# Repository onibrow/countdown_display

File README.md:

# Countdown Display

A low power countdown display

## Manual

### On / Off

The slide switch in the right position (closer to the edge of the device) is the "Discharge" or ON mode. The slide switch in the left position (closer to the middle of the device) is the "Charge / OFF" mode.

### Charging

To charge the battery, put the slide switch into the "Charge / OFF" mode - this will disconnect the battery from the rest of the device and enable it to be charged. At this state, the display will no longer turn on. Plug in a microUSB cable to the port and watch the indicator LED turn on. If RED, the battery is charging - if GREEN, the charge is complete. From fully discharged to fully charged, it will take about 2.5 hours.

### Safety

As this device has all of its electrical components exposed, do not touch this with wet hands or poke it with metal / conductive objects. There are safety electronics in play to prevent the battery from over-currenting and frying itself, it is generally not a great idea to mess around with LiPo batteries. 

## Features

### 128x32 OLED Display

[SSD1306](https://smile.amazon.com/gp/product/B07X35H728/ref=ppx_yo_dt_b_asin_title_o06_s00?ie=UTF8&psc=1) 128x32 OLED display compatible with Adafruit's [OLED library](https://github.com/adafruit/Adafruit_SSD1306), featuring a shut down mode for low power consumption, capable of running off 3.6V to 5V.

### Low Power

ATMega328P was chosen for the microcontroller of choice, for its low power sleep feature and small footprint. Running off of a LiPo battery, it can enter a deep sleep that consumes less that 10uA of current utilizing the external interrupt (generated using a push button) based indefinite sleep, from the [Arduino LowPower library](https://www.arduino.cc/en/Reference/ArduinoLowPower). The fuses are burned to use an 8MHz external clock and to brown out at 3V.

### RTC

A real time clock was used to keep track of the current date and time, running off of an ultra low power DS3231 and a back up coin cell. With the coin cell, the time keeping feature can run for 5 years, while the ultra low power could be directly sourced from one of the digital output pins on the ATMega to make power on and off of the RTC much easier. The Adafrtui [RTClib](https://github.com/adafruit/RTClib) was used for this chip.

### LiPo

A 40mAh LiPo battery was chosen as the main power supply for this device. Considering an ON current of about 12mA and a deep sleep current of 10uA, a quick calculation assuming that the device will be powered on for 2 minutes in any given day leaves the device an astounding 2 month life on a single charge. It is also equiped with an [MCP73831](https://www.microchip.com/wwwproducts/en/en024903) single cell, LiPo charge management controller to recharge the battery safely over a microUSB connection.

## Gallery

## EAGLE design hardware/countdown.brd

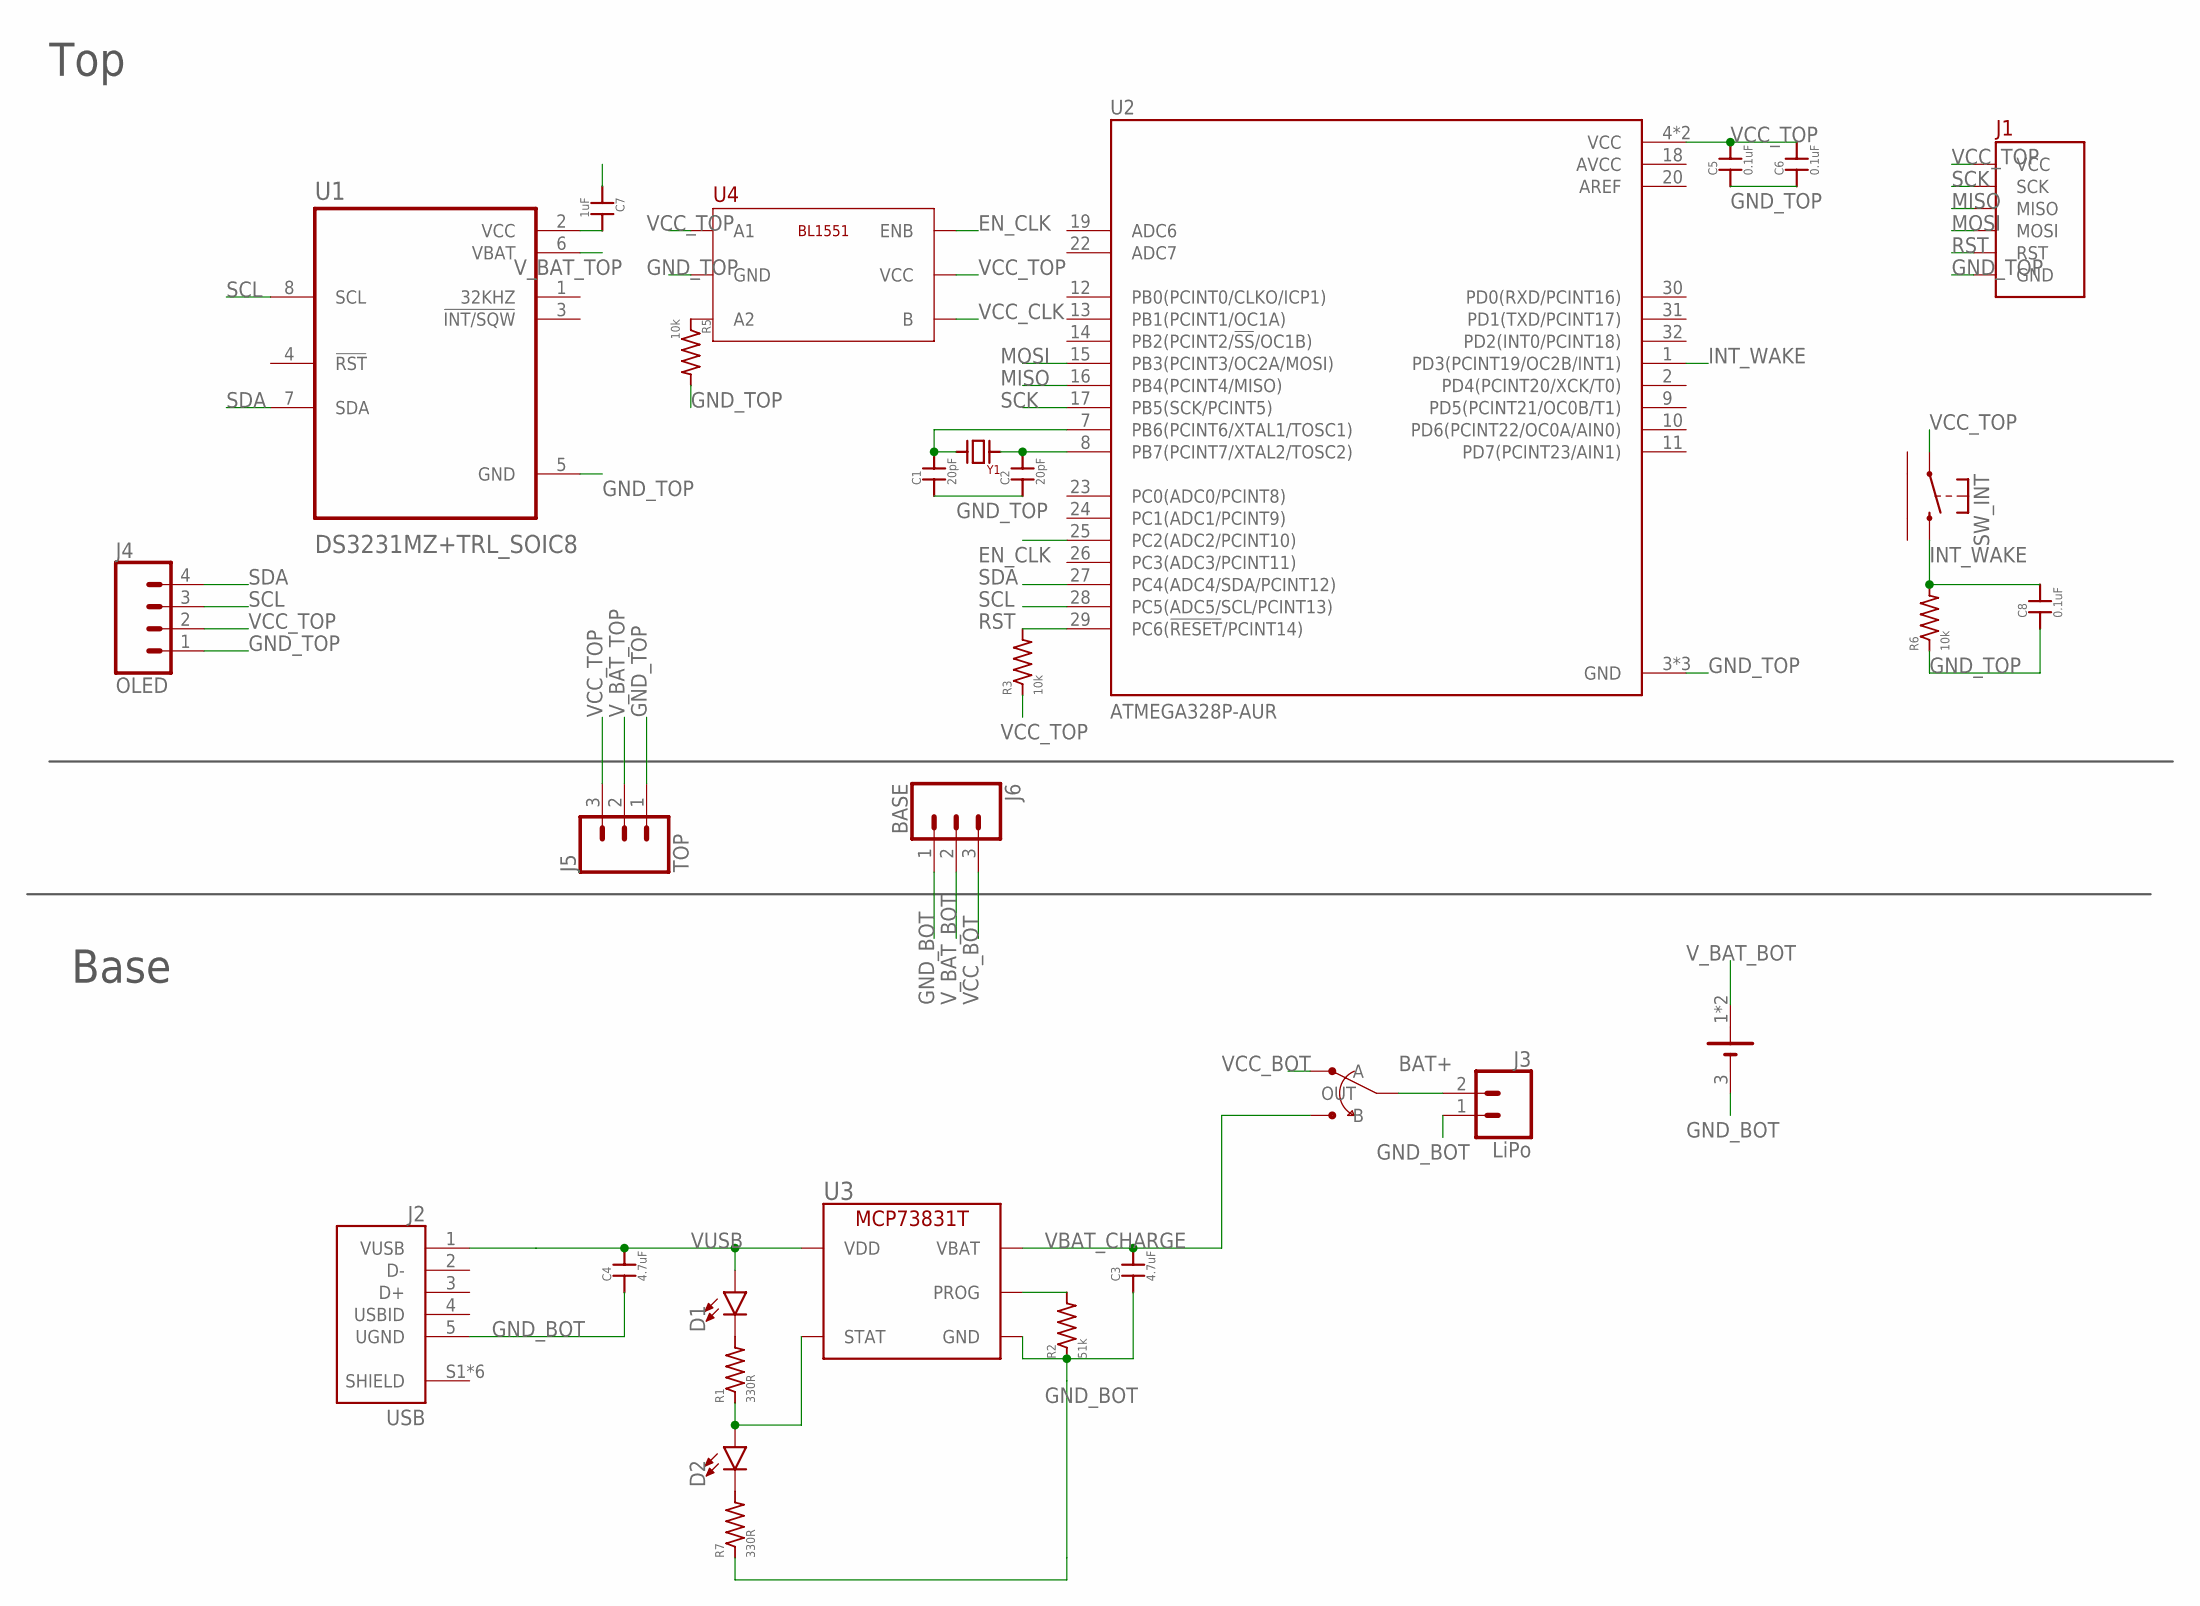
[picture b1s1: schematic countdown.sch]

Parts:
BT1: BK-916-TR; BAT_BK-916-TR
C1, C2: 20pF; 0402-CAP
C3, C4: 4.7uF; 0402-CAP
C5, C6, C8: 0.1uF; 0402-CAP
C7: 1uF; 0402-CAP
D1, D2: LED0603; LED-0603
J1: BURNIN
J2: USB; FCI_10103594-0001LF
J3: LiPo; 1X02
J4: OLED; 1X04_NO_SILK
J5: TOP; 1X03_NO_SILK
J6: BASE; 1X03_NO_SILK
R1, R7: 330R; R0402
R2: 51k; R0402
R3, R5, R6: 10k; R0402
SW_INT: FSMRACD
U1: DS3231MZ+TRL_SOIC8; SOIC-8
U2: ATMEGA328P-AUR; QFP80P900X900X120-32N
U3: MCP73831T; SOT-23-5
U4: BL1551; SOT-363
U$1: CL-SB-12C-12; 12C-12
Y1: CRYSTAL_5032; XTAL500X320X130N

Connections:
AREF: U2.20 (AREF)
AVCC: U2.18 (AVCC)
BAT+: J3.2, U$1.2 (OUT)
EN_CLK: U2.25 (PC2(ADC2/PCINT10)), U4.6 (ENB)
GND_BOT: BT1.3 (-), C3.1, C4.1, J2.5 (UGND), J3.1, J6.1, R2.1, R7.1, U3.2 (GND)
GND_TOP: C1.1, C2.1, C5.1, C6.1, C7.1, C8.1, J1.GND, J4.1, J5.1, R5.2, R6.1, U1.5 (GND), U2.3 (GND), U2.5 (GND), U2.21 (GND), U4.2 (GND)
INT_WAKE: C8.2, R6.2, SW_INT.P$2 (S), U2.1 (PD3(PCINT19/OC2B/INT1))
MISO: J1.MISO, U2.16 (PB4(PCINT4/MISO))
MOSI: J1.MOSI, U2.15 (PB3(PCINT3/OC2A/MOSI))
unnamed: R5.1, U4.3 (A2)
unnamed: D2.C, R7.2
unnamed: D1.C, R1.2
PROG: R2.2, U3.5 (PROG)
RST: J1.RST, R3.2, U2.29 (PC6(!RESET!/PCINT14))
SCK: J1.SCK, U2.17 (PB5(SCK/PCINT5))
SCL: J4.3, U1.8 (SCL), U2.28 (PC5(ADC5/SCL/PCINT13))
SDA: J4.4, U1.7 (SDA), U2.27 (PC4(ADC4/SDA/PCINT12))
STAT: D2.A, R1.1, U3.1 (STAT)
VBAT_CHARGE: C3.2, U3.3 (VBAT), U$1.3 (B)
VCC_BOT: J6.3, U$1.1 (A)
VCC_CLK: C7.2, U1.2 (VCC), U4.4 (B)
VCC_TOP: C5.2, C6.2, J1.3.3V (VCC), J4.2, J5.3, R3.1, SW_INT.P$1, U2.4 (VCC), U2.6 (VCC), U4.1 (A1), U4.5 (VCC)
VUSB: C4.2, D1.A, J2.1 (VUSB), U3.4 (VDD)
V_BAT_BOT: BT1.1 (+), BT1.2 (+), J6.2
V_BAT_TOP: J5.2, U1.6 (VBAT)
XTAL1: C1.2, U2.7 (PB6(PCINT6/XTAL1/TOSC1)), Y1.2 (B)
XTAL2: C2.2, U2.8 (PB7(PCINT7/XTAL2/TOSC2)), Y1.1 (A)

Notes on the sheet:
Top
Base

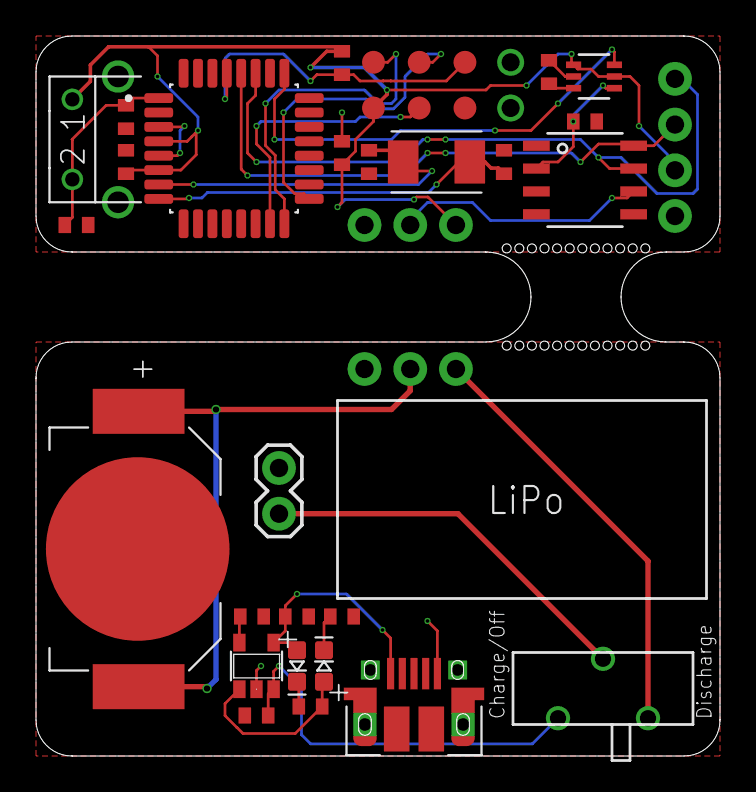
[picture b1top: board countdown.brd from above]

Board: 2 copper layers, 38.0 x 40.0 mm, 30 parts (1 on the bottom side), 25 nets.

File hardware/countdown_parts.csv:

Designator,Mid X,Mid Y,Layer,Rotation,Comment,Footprint,LCSC Part
C1,23.5,33,Top,90,20pF,402,C1554
C2,31,33,Top,90,20pF,402,C1554
C3,17.25,2.25,Top,0,4.7uF,402,C23733
C4,19.5,7.75,Top,0,4.7uF,402,C23733
C5,22,33.5,Top,90,0.1uF,402,C1525
C6,10,33,Top,90,0.1uF,402,C1525
C7,35.5,35.25,Top,0,1uF,402,C52923
C8,7.25,29.5,Top,0,0.1uF,402,C1525
D1,19.5,5,Top,90,Red,LED_0603,C2286
D2,21,5,Top,270,Green,LED_0603,C72043
R1,20.25,2.75,Top,0,330R,402,C25104
R2,17,7.75,Top,0,51k,402,C25794
R3,22,38.5,Top,90,10k,402,C11702
R5,33.5,38,Top,90,10k,402,C25744
R6,10,35.5,Top,90,10k,402,C25744
R7,22,7.75,Top,0,330R,402,C25104
U1,35.5,32,Top,270,DS3231,SOIC-8_3.9x4.9x1.27P,C107410
U2,16,33.75,Top,270,ATMEGA328P,TQFP-32_7.0x7.0x0.8P,C14877
U3,17.25,5,Top,270,MCP73831,SOT-23-5,C424093
U4,36,37.75,Top,0,BL1551,SOT-363,C82528
Y1,27.25,33,Top,0,8Mhz,SMD-5032_2P,C115962

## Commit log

2020-05-29 more pusheen progress
2020-05-29 add more build files to ignore
2020-05-29 Fix compilations and add more squish to pusheen
2020-05-29 add oled text test
2020-05-30 add smoother animations
2020-05-31 start hardware
2020-06-01 make debug version
2020-06-02 prepare for order
2020-06-03 start final firmware
2020-06-10 jlc order done
2020-06-12 small fixes to board from debugging
2020-06-12 more firmware changes
2020-06-13 finish??
2020-06-14 working firmware
2020-06-17 fix sleep bounce
2020-06-17 last flash
2020-06-19 reorganize test sketches, add schematic pdf
2020-06-19 rename firmware
2020-06-19 Add photos
